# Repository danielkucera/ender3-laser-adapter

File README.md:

# ender3-laser-adapter
Adapter for connecting a laser to output for part cooling fan on Ender 3

[Gerbers can be found here.](./output/gerber/)

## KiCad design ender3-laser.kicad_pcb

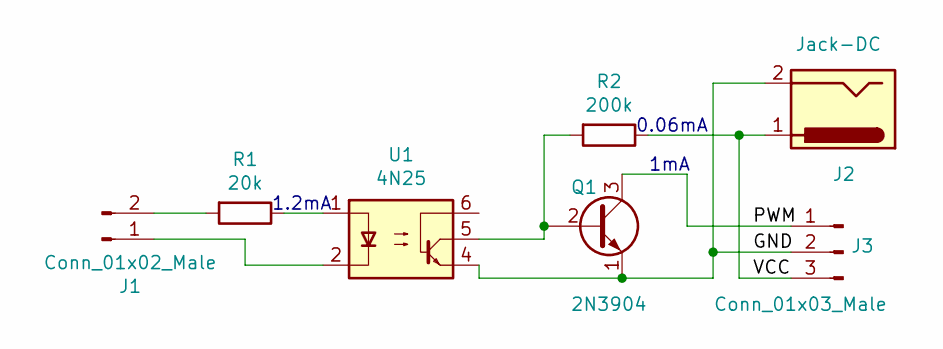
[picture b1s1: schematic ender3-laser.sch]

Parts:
J1: Conn_01x02_Male; JST_XH_B2B-XH-A_1x02_P2.50mm_Vertical
J2: Jack-DC; BarrelJack_CUI_PJ-063AH_Horizontal
J3: Conn_01x03_Male; PinSocket_1x03_P2.54mm_Horizontal
Q1: 2N3904; TO-92_Inline
R1: 20k; R_Axial_DIN0207_L6.3mm_D2.5mm_P7.62mm_Horizontal
R2: 200k; R_Axial_DIN0207_L6.3mm_D2.5mm_P7.62mm_Horizontal
U1: 4N25; DIP-6_W7.62mm

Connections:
/GND: J2.2, J3.2, Q1.1 (E), U1.4
/PWM: J3.1, Q1.3 (C)
/VCC: J2.1, J3.3, R2.1
unnamed: J1.1, U1.2
unnamed: J1.2, R1.2
unnamed: Q1.2 (B), R2.2, U1.5
unnamed: R1.1, U1.1

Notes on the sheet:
1mA
0.06mA
1.2mA

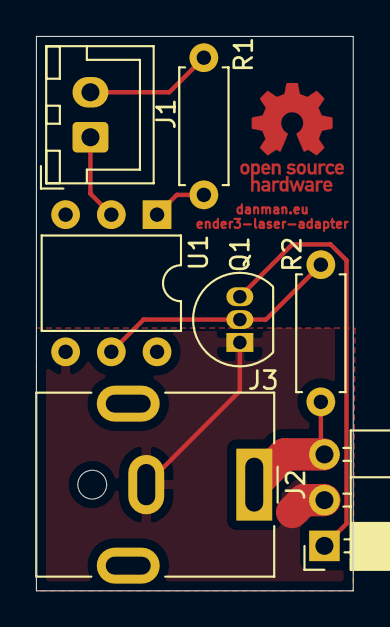
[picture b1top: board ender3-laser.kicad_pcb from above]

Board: 2 copper layers, 17.6 x 30.8 mm, 7 parts (0 on the bottom side), 7 nets.

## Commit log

2020-07-26 first version
2020-07-26 added outputs
